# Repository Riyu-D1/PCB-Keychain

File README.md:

# PCB-Keychain
A simple yet cool and functional pcb keychain. Exactly what it sounds like!

## What it is
A small keychain about the size of a 2.36" colour e-ink screen. The screen sits flat on the front of the board, and there are four little RGB LEDs, two on each side, so it lights up whichever way it's hanging.

I kept it simple on purpose. The brains are an ESP32-C3 SuperMini, a tiny dev board that already has USB-C, a regulator and a boot button on it, so I just solder it onto the back with headers. The e-ink screen comes on Waveshare's driver board and plugs into an 8-pin header at the top.

It runs off a small LiPo. A TP4056 charges it from the SuperMini's USB-C, a slide switch turns it on and off, and a diode lets the battery power the board when it's unplugged. Because e-ink keeps its picture with no power, the battery lasts a long time.

## Parts
Full list in [bom.csv](bom.csv).

Cost: about $28.35 USD for one keychain (single-unit prices from LCSC, Waveshare, Tindie and Adafruit, not counting the PCB, shipping or LCSC minimum order quantities).

- ESP32-C3 SuperMini
- Waveshare 2.36" e-Paper Module (G)
- 4x SK6812MINI LEDs
- TP4056 charger, SS14 diode, slide switch
- JST-PH 2-pin LiPo connector
- A few 0603 caps and one resistor

## Files
KiCad project is in `kicad/`. Open `keychain.kicad_pro`.

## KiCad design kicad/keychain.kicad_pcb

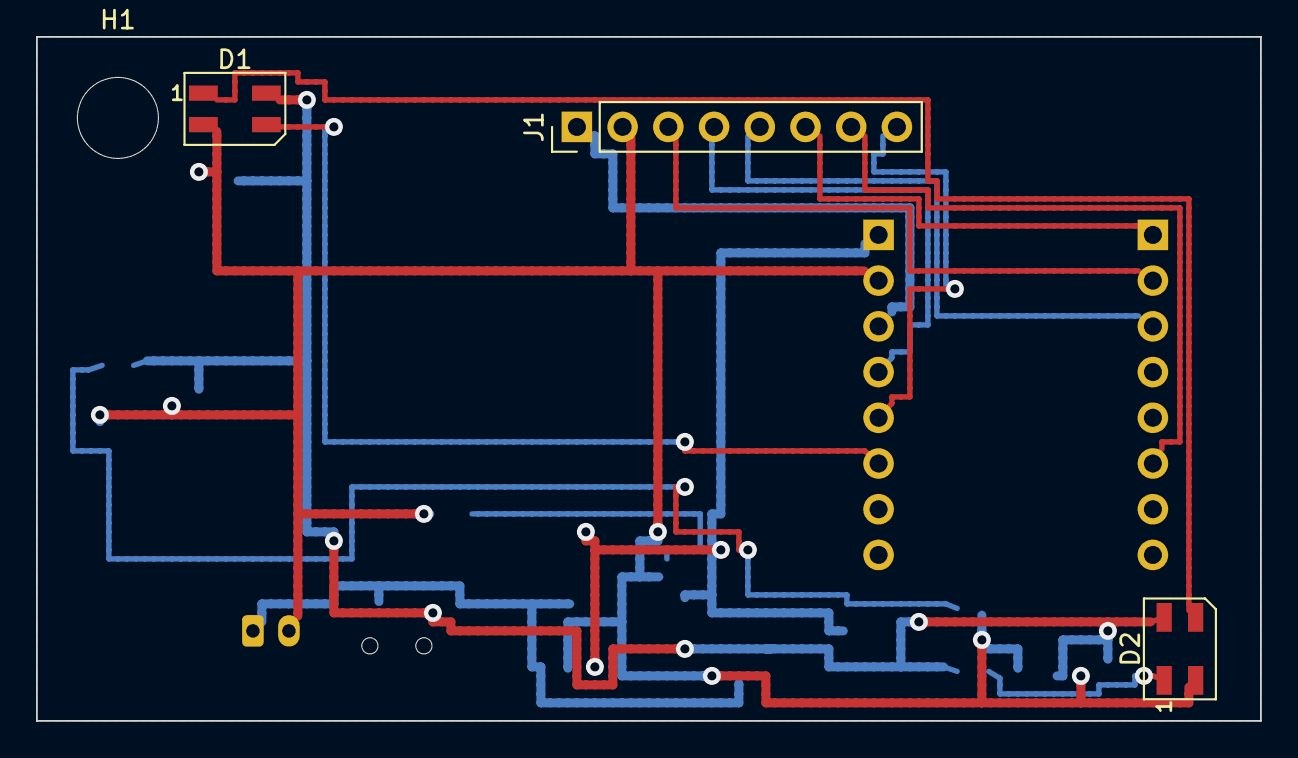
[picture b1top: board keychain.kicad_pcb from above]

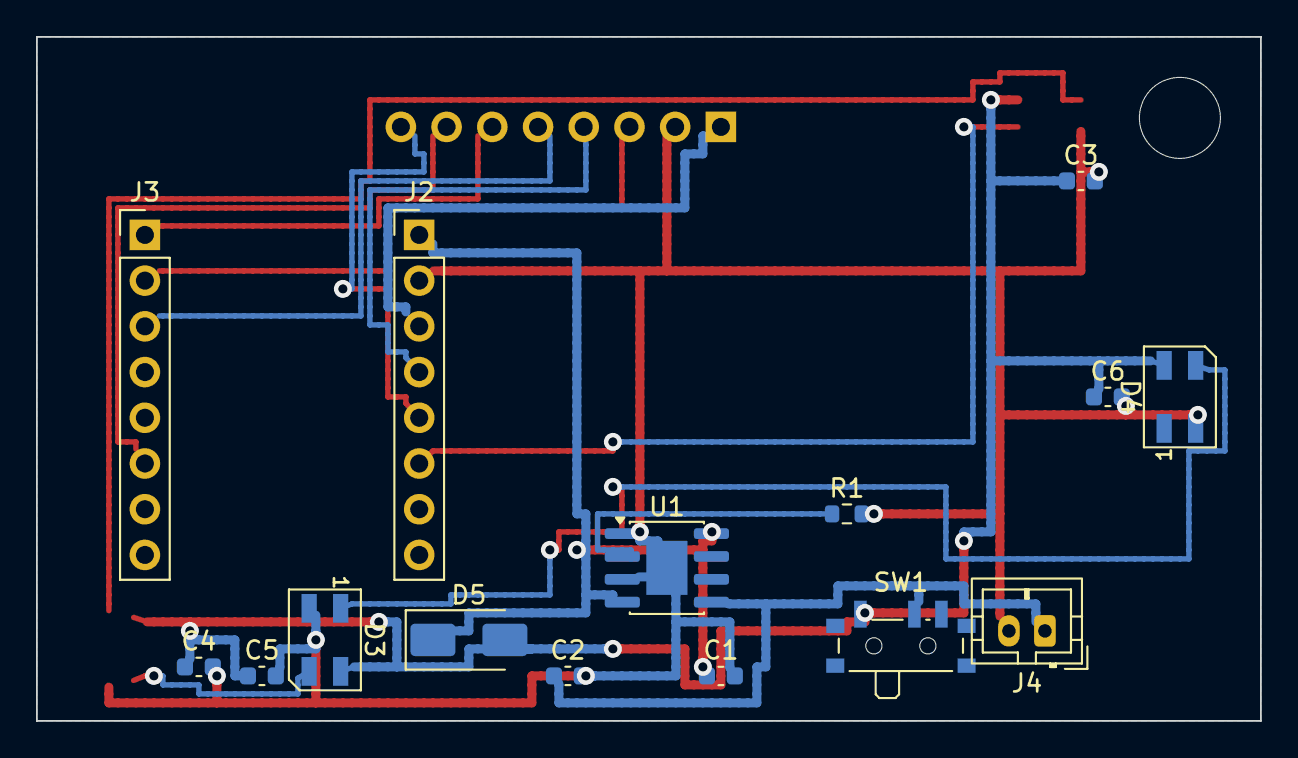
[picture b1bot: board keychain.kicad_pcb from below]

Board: 2 copper layers, 68.0 x 38.0 mm, 19 parts (15 on the bottom side), 16 nets.

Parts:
C1, C2: 10uF; C_0603_1608Metric
C3, C4, C5, C6: 100nF; C_0603_1608Metric
D1, D2, D3, D4: SK6812MINI; LED_SK6812MINI_PLCC4_3.5x3.5mm_P1.75mm
D5: SS14; D_SMA
H1: MountingHole_4.5mm
J1: EPAPER; PinHeader_1x08_P2.54mm_Vertical
J2: SuperMini-L; PinHeader_1x08_P2.54mm_Vertical
J3: SuperMini-R; PinHeader_1x08_P2.54mm_Vertical
J4: BATTERY; JST_PH_B2B-PH-K_1x02_P2.00mm_Vertical
R1: 1.2k; R_0603_1608Metric
SW1: SW_SPDT; SW_SPDT_PCM12
U1: TP4056; SOIC-8-1EP_3.9x4.9mm_P1.27mm_EP2.29x3mm

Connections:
+3.3V: J1.1, J2.3
+5V: C1.1, D5.1, J2.1, U1.4, U1.8
D1_DO: D1.1, D2.3
D2_DO: D2.1, D3.3
D3_DO: D3.1, D4.3
EPD_BUSY: J1.8, J2.5
EPD_CLK: J1.4, J2.4
EPD_CS: J1.5, J3.3
EPD_DC: J1.6, J3.1
EPD_MOSI: J1.3, J3.2
EPD_RST: J1.7, J3.6
GND: C1.2, C2.2, C3.2, C4.2, C5.2, C6.2, D1.2, D2.2, D3.2, D4.2, J1.2, J2.2, J4.2, R1.2, U1.1, U1.3, U1.9
LED_DATA: D1.3, J2.6
PROG: R1.1, U1.2
VBAT: C2.1, J4.1, SW1.2, U1.5
VBAT_SW: C3.1, C4.1, C5.1, C6.1, D1.4, D2.4, D3.4, D4.4, D5.2, SW1.1

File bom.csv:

Reference,Value,Footprint,Quantity,Supplier,Supplier Part,Unit Price (USD),Line Total (USD),Link
"C1,C2",10uF,Capacitor_SMD:C_0603_1608Metric,2,LCSC,C19702,0.0308,0.0616,https://www.lcsc.com/product-detail/C19702.html
"C3,C4,C5,C6",100nF,Capacitor_SMD:C_0603_1608Metric,4,LCSC,C14663,0.0141,0.0564,https://www.lcsc.com/product-detail/C14663.html
"D1,D2,D3,D4",SK6812MINI,LED_SMD:LED_SK6812MINI_PLCC4_3.5x3.5mm_P1.75mm,4,LCSC,C5149201,0.0810,0.3240,https://www.lcsc.com/product-detail/C5149201.html
D5,SS14,Diode_SMD:D_SMA,1,LCSC,C2480,0.0192,0.0192,https://www.lcsc.com/product-detail/C2480.html
J1,1x8 2.54mm header (EPAPER),Connector_PinHeader_2.54mm:PinHeader_1x08_P2.54mm_Vertical,1,LCSC,C2337,0.1599,0.1599,https://www.lcsc.com/product-detail/C2337.html
"J2,J3","1x8 2.54mm header (SuperMini, cut from J1's 1x40 strip)",Connector_PinHeader_2.54mm:PinHeader_1x08_P2.54mm_Vertical,2,LCSC,C2337,0.0000,0.0000,https://www.lcsc.com/product-detail/C2337.html
J4,JST PH 2-pin B2B-PH-K,Connector_JST:JST_PH_B2B-PH-K_1x02_P2.00mm_Vertical,1,LCSC,C131337,0.0357,0.0357,https://www.lcsc.com/product-detail/C131337.html
R1,1.2k,Resistor_SMD:R_0603_1608Metric,1,LCSC,C22765,0.0034,0.0034,https://www.lcsc.com/product-detail/C22765.html
SW1,PCM12 SPDT slide switch,Button_Switch_SMD:SW_SPDT_PCM12,1,LCSC,C221841,1.2754,1.2754,https://www.lcsc.com/product-detail/C221841.html
U1,TP4056,Package_SO:SOIC-8-1EP_3.9x4.9mm_P1.27mm_EP2.29x3mm,1,LCSC,C16581,0.1862,0.1862,https://www.lcsc.com/product-detail/C16581.html
(off-board),ESP32-C3 SuperMini,,1,Tindie (Maker go),adz1122,3.9000,3.9000,https://www.tindie.com/products/adz1122/esp32-c3-development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
(off-board),Waveshare 2.36inch e-Paper Module (G),,1,Waveshare,2.36inch e-Paper Module (G),15.1900,15.1900,https://www.waveshare.com/2.36inch-e-paper-module-g.htm
(off-board),LiPo 3.7V 400mAh with JST-PH,,1,Adafruit,3898,6.9500,6.9500,https://www.adafruit.com/product/3898
TOTAL,,,,,,,28.16,
